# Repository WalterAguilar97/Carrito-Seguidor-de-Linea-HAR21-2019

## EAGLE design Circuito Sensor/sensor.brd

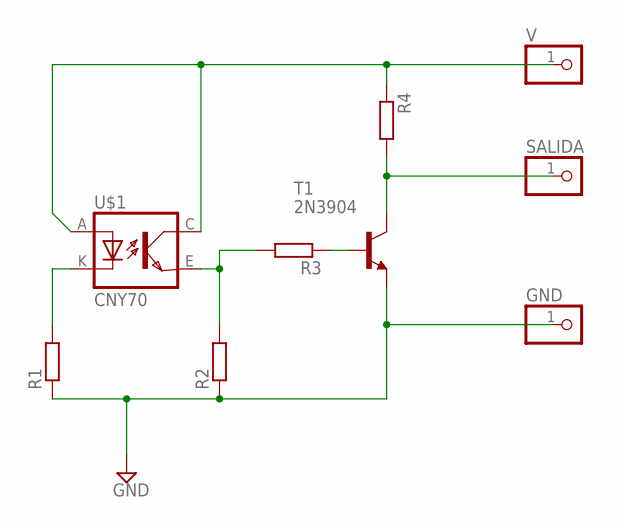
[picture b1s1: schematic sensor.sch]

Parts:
GND: PINHD-1X1; 1X01
R1, R2, R3, R4: R-EU_0207/10; 0207/10
SALIDA: PINHD-1X1; 1X01
T1: 2N3904; TO92
U$1: CNY70; 4
V: PINHD-1X1; 1X01

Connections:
GND: GND.1, R1.1, R2.1, T1.3 (E)
unnamed: R2.2, R3.2, U$1.E (EMI)
unnamed: R1.2, U$1.K (C)
unnamed: R3.1, T1.2 (B)
unnamed: R4.1, U$1.A, U$1.C (COL), V.1
unnamed: R4.2, SALIDA.1, T1.1 (C)

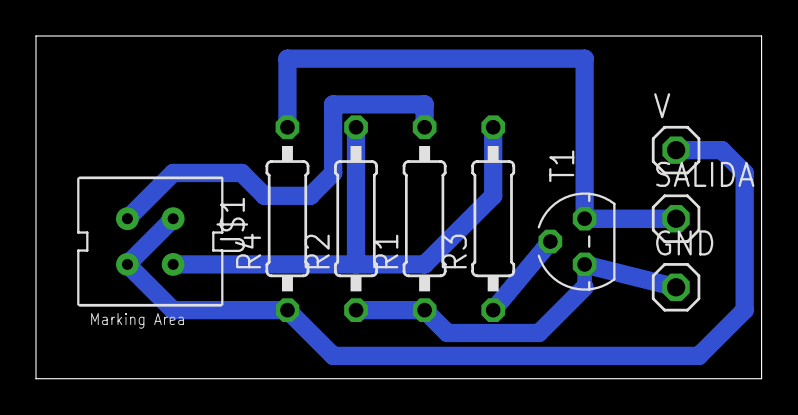
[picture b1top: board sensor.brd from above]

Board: 2 copper layers, 40.3 x 19.0 mm, 9 parts (0 on the bottom side), 6 nets.
